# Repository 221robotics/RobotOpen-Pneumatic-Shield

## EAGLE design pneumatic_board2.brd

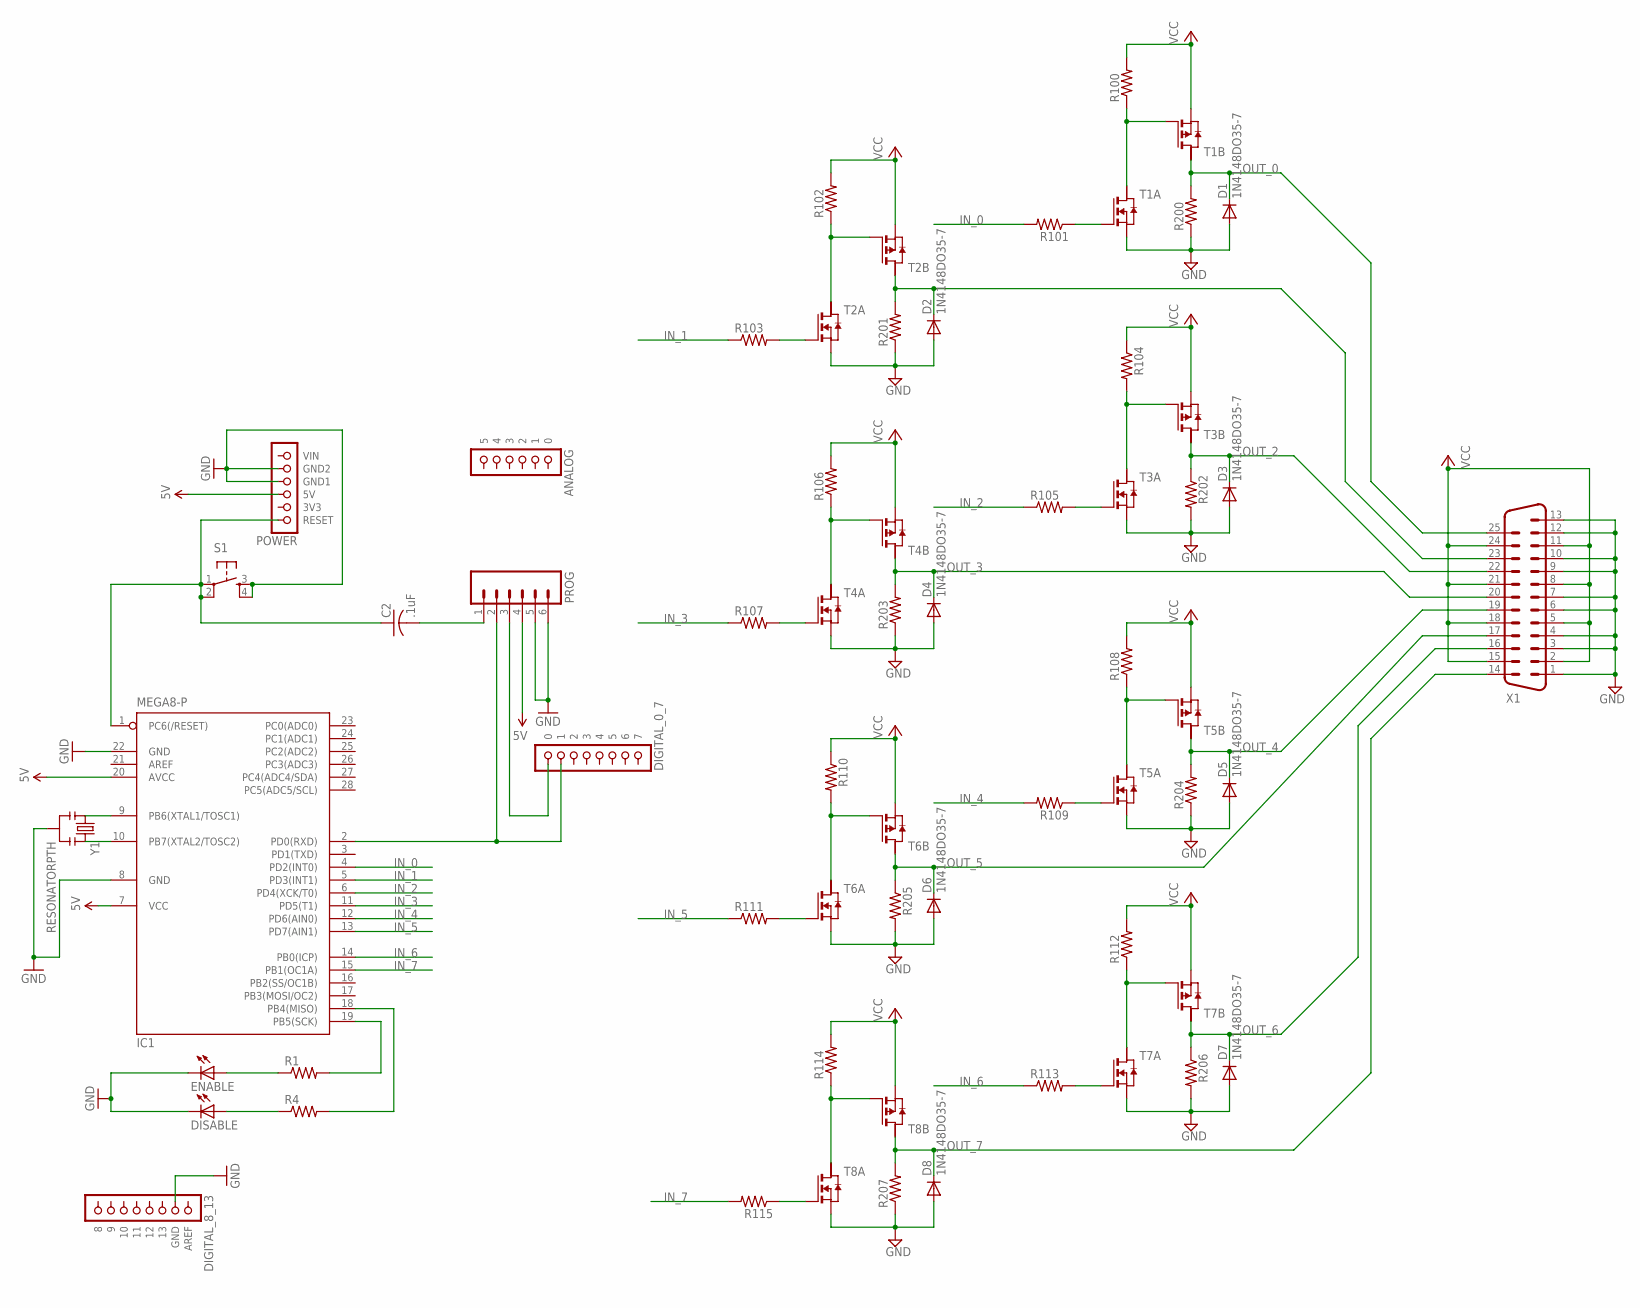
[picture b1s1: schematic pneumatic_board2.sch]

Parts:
C2: .1uF; C025-024X044
D1, D2, D3, D4, D5, D6, D7, D8: 1N4148DO35-7; DO35-7
DISABLE: LED5MM
ENABLE: LED5MM
IC1: MEGA8-P; DIL28-3
PROG: M06SIP_LOCK; 1X06-SIP_LOCK
R1, R4, R100, R101, R102, R103, R104, R105, R106, R107, R108, R109, R110, R111, R112, R113, R114, R115, R200, R201, R202, R203, R204, R205, R206, R207: RESISTORAXIAL-0.3; AXIAL-0.3
S1: TAC_SWITCHPTH; TACTILE-PTH
T1, T2, T3, T4, T5, T6, T7, T8: PN_MOSFET-SO8; SO8
U$1: POWER; 1X06
U$2: ANALOG; 1X06
U$3: DIGITAL_0_7; 1X08
U$4: DIGITAL_8_13; 1X08
X1: M25VP
Y1: RESONATORPTH; RESONATOR-PTH

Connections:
5V: IC1.7 (VCC), IC1.20 (AVCC), PROG.4, U$1.3 (5V)
GND: D1.A, D2.A, D3.A, D4.A, D5.A, D6.A, D7.A, D8.A, DISABLE.K (C), ENABLE.K (C), IC1.8 (GND), IC1.22 (GND), PROG.5, PROG.6, R200.P$1 (1), R201.P$1 (1), R202.P$2 (2), R203.P$1 (1), R204.P$1 (1), R205.P$2 (2), R206.P$2 (2), R207.P$1 (1), S1.3, S1.4, T1.1 (S), T2.1 (S), T3.1 (S), T4.1 (S), T5.1 (S), T6.1 (S), T7.1 (S), T8.1 (S), U$1.4 (GND1), U$1.5 (GND2), U$4.2 (GND), X1.1, X1.3, X1.4, X1.6, X1.7, X1.9, X1.10, X1.12, X1.13, Y1.2
IN_0: IC1.4 (PD2(INT0)), R101.P$2 (2)
IN_1: IC1.5 (PD3(INT1)), R103.P$1 (1)
IN_2: IC1.6 (PD4(XCK/T0)), R105.P$1 (1)
IN_3: IC1.11 (PD5(T1)), R107.P$1 (1)
IN_4: IC1.12 (PD6(AIN0)), R109.P$2 (2)
IN_5: IC1.13 (PD7(AIN1)), R111.P$1 (1)
IN_6: IC1.14 (PB0(ICP)), R113.P$1 (1)
IN_7: IC1.15 (PB1(OC1A)), R115.P$2 (2)
unnamed: IC1.2 (PD0(RXD)), PROG.2, U$3.7 (1)
unnamed: IC1.9 (PB6(XTAL1/TOSC1)), Y1.1
unnamed: IC1.10 (PB7(XTAL2/TOSC2)), Y1.3
unnamed: IC1.19 (PB5(SCK)), R1.P$2 (2)
unnamed: IC1.18 (PB4(MISO)), R4.P$2 (2)
unnamed: R100.P$1 (1), T1.4 (G), T1.7 (D)
unnamed: R101.P$1 (1), T1.2 (G)
unnamed: R104.P$2 (2), T3.4 (G), T3.7 (D)
unnamed: R102.P$1 (1), T2.4 (G), T2.7 (D)
unnamed: R103.P$2 (2), T2.2 (G)
unnamed: R105.P$2 (2), T3.2 (G)
unnamed: R106.P$1 (1), T4.4 (G), T4.7 (D)
unnamed: R107.P$2 (2), T4.2 (G)
unnamed: R108.P$1 (1), T5.4 (G), T5.7 (D)
unnamed: R109.P$1 (1), T5.2 (G)
unnamed: R110.P$2 (2), T6.4 (G), T6.7 (D)
unnamed: R111.P$2 (2), T6.2 (G)
unnamed: PROG.3, U$3.8 (0)
unnamed: ENABLE.A, R1.P$1 (1)
unnamed: DISABLE.A, R4.P$1 (1)
unnamed: R112.P$1 (1), T7.4 (G), T7.7 (D)
unnamed: R113.P$2 (2), T7.2 (G)
unnamed: R114.P$1 (1), T8.4 (G), T8.7 (D)
unnamed: R115.P$1 (1), T8.2 (G)
unnamed: C2.2, PROG.1
unnamed: C2.1, IC1.1 (PC6(/RESET)), S1.1, S1.2, U$1.1 (RESET)
OUT_0: D1.C, R200.P$2 (2), T1.5 (D), X1.25
OUT_1: D2.C, R201.P$2 (2), T2.5 (D), X1.23
OUT_2: D3.C, R202.P$1 (1), T3.5 (D), X1.22
OUT_3: D4.C, R203.P$2 (2), T4.5 (D), X1.20
OUT_4: D5.C, R204.P$2 (2), T5.5 (D), X1.19
OUT_5: D6.C, R205.P$1 (1), T6.5 (D), X1.17
OUT_6: D7.C, R206.P$1 (1), T7.5 (D), X1.16
OUT_7: D8.C, R207.P$2 (2), T8.5 (D), X1.14
VCC: R100.P$2 (2), R102.P$2 (2), R104.P$1 (1), R106.P$2 (2), R108.P$2 (2), R110.P$1 (1), R112.P$2 (2), R114.P$2 (2), T1.3 (S), T2.3 (S), T3.3 (S), T4.3 (S), T5.3 (S), T6.3 (S), T7.3 (S), T8.3 (S), X1.2, X1.5, X1.8, X1.11, X1.15, X1.18, X1.21, X1.24

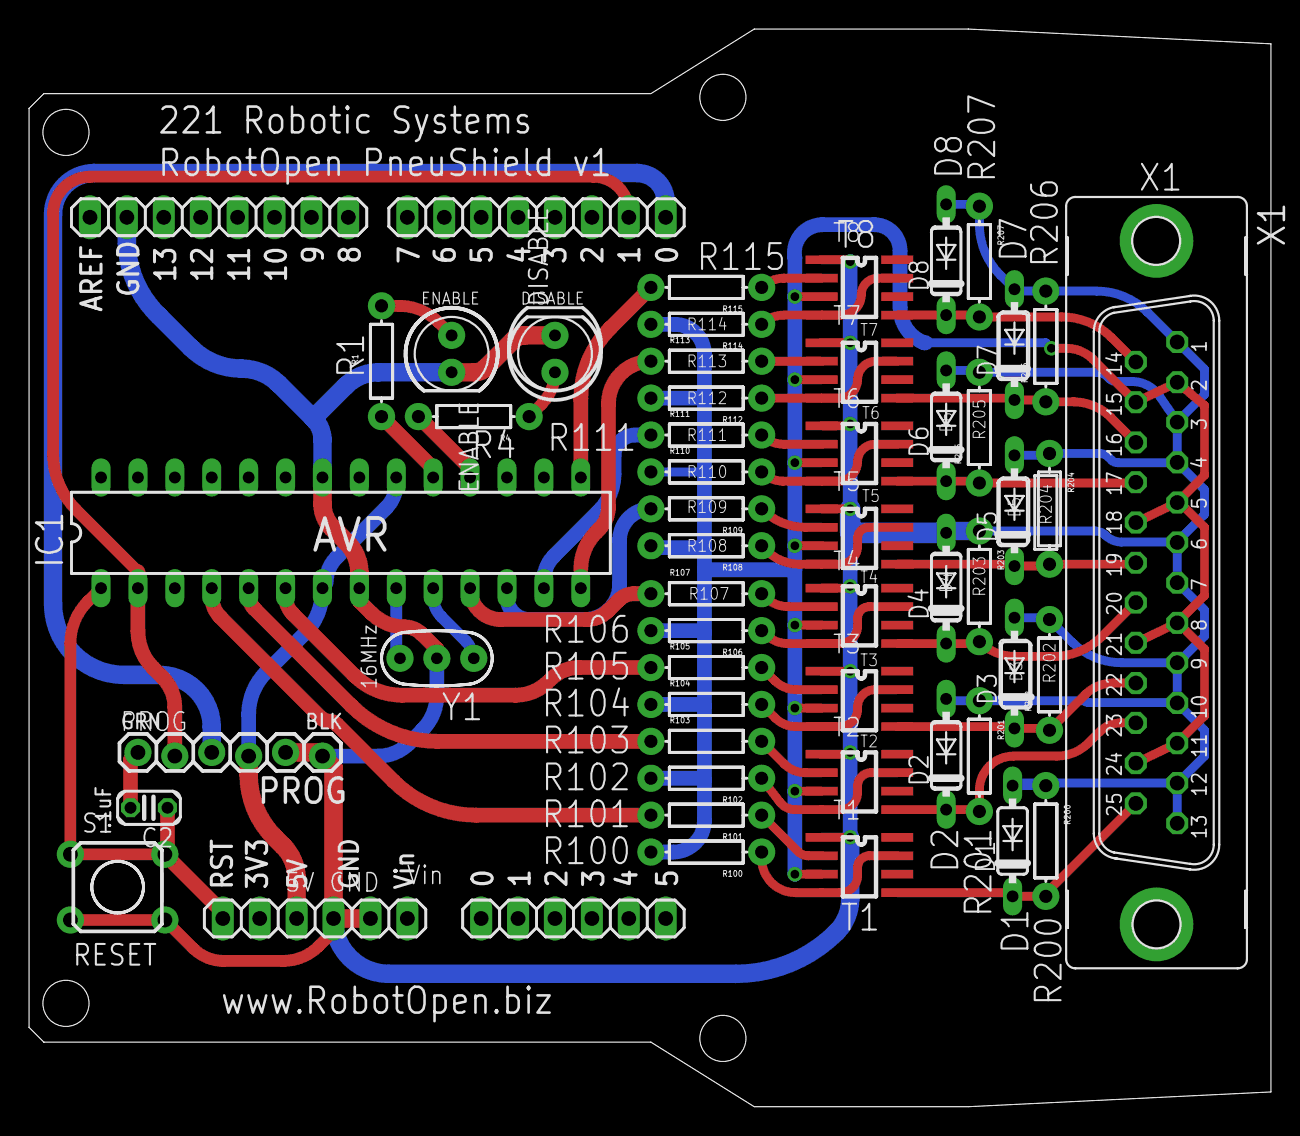
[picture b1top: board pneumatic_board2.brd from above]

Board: 2 copper layers, 85.5 x 74.2 mm, 54 parts (0 on the bottom side), 45 nets.

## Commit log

2012-09-11 Initial commit - order sent to Sunstone.
2012-09-12 Removed old files.
2013-02-18 Added code for atmega chip.
